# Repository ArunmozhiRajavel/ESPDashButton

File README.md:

# ESPDashButton
Contains the eagle files of ESPDash button

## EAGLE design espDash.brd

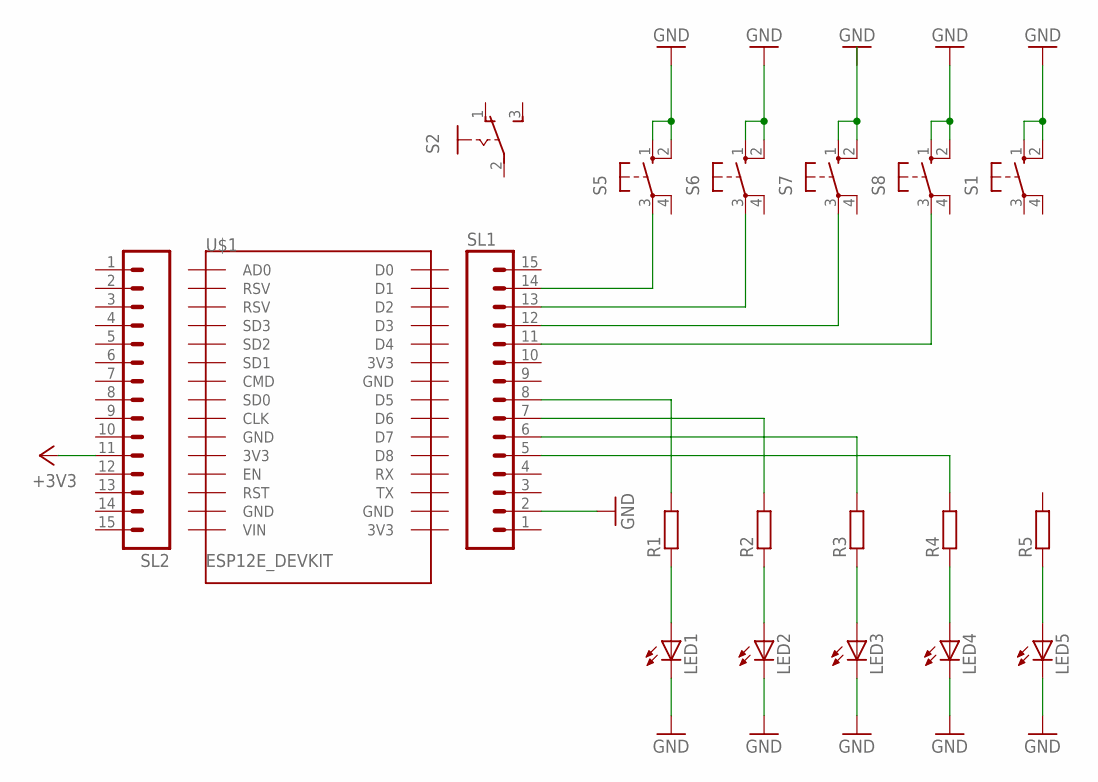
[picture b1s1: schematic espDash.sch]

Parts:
LED1, LED2, LED3, LED4, LED5: LED5MM
R1, R2, R3, R4, R5: R-EU_0207/10; 0207/10
S1, S5, S6, S7, S8: 40-XX; B3F-40XX
S2: M251
SL1, SL2: M15; 15P
U$1: ESP12E_DEVKIT

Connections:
+3V3: SL2.11
GND: LED1.K (C), LED2.K (C), LED3.K (C), LED4.K (C), LED5.K (C), S1.1 (S), S1.2 (S1), S5.1 (S), S5.2 (S1), S6.1 (S), S6.2 (S1), S8.1 (S), S8.2 (S1), SL1.2
unnamed: S5.3, SL1.14
unnamed: S6.3, SL1.13
unnamed: S7.3, SL1.12
unnamed: S8.3, SL1.11
unnamed: R1.2, SL1.8
unnamed: R2.2, SL1.7
unnamed: R3.2, SL1.6
unnamed: R4.2, SL1.5
unnamed: LED3.A, R3.1
unnamed: LED4.A, R4.1
unnamed: S7.1 (S), S7.2 (S1)
unnamed: LED1.A, R1.1
unnamed: LED5.A, R5.1
unnamed: LED2.A, R2.1

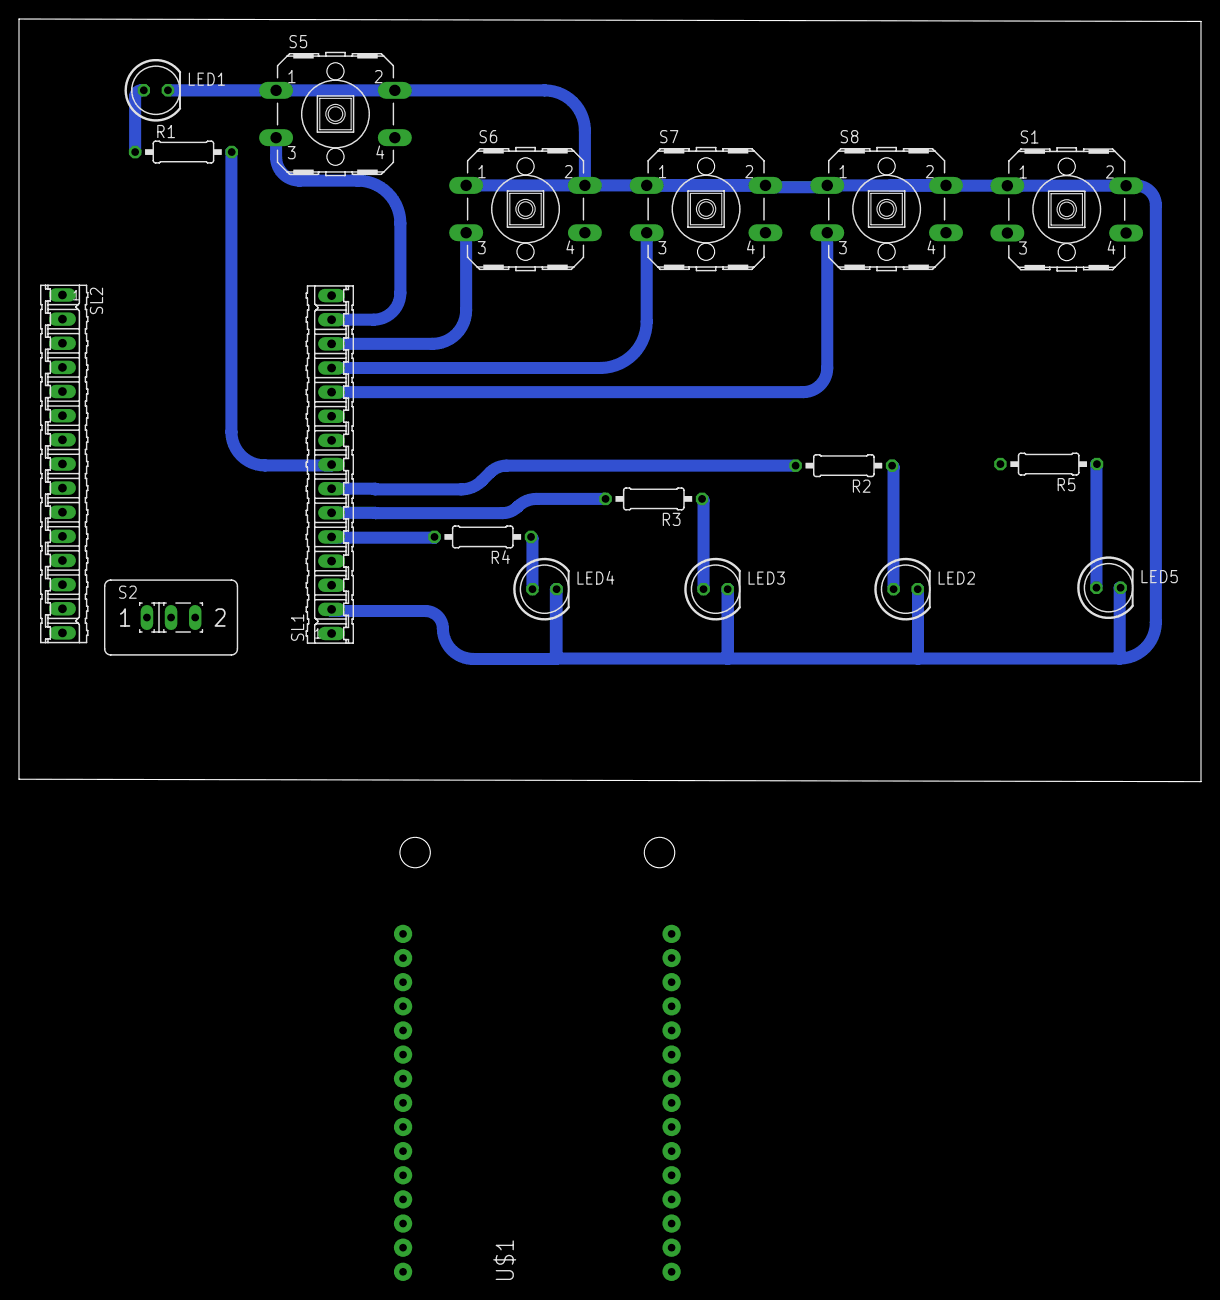
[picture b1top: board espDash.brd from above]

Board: 2 copper layers, 124.4 x 80.3 mm, 19 parts (0 on the bottom side), 15 nets.

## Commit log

2016-09-16 Initial upload
    Eagle Files with 4 buttons
2016-09-16 5 button
    Added a button
